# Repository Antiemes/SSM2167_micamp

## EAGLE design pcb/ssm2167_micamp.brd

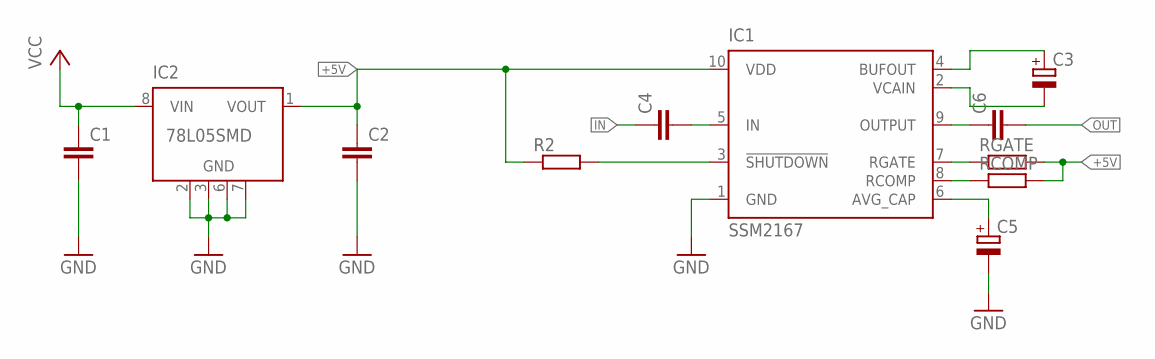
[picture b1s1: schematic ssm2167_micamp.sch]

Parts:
C1, C2: C-EUC0603K; C0603K
C3, C5: CPOL-EUE; PANASONIC_E
C4, C6: C-EUC1812; C1812
IC1: SSM2167; SO10
IC2: 78L05SMD; SO08
R2: R-EU_M1206; M1206
RCOMP: R-EU_M1206; M1206
RGATE: R-EU_M1206; M1206

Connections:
+5V: C2.1, IC1.10 (VDD), IC2.1 (VOUT), R2.1, RCOMP.2, RGATE.2
GND: C1.2, C2.2, C5.-, IC1.1 (GND), IC2.2 (GND), IC2.3 (GND), IC2.6 (GND), IC2.7 (GND)
IN: C4.1
unnamed: IC1.3 (!SHUTDOWN), R2.2
unnamed: IC1.7 (RGATE), RGATE.1
unnamed: IC1.8 (RCOMP), RCOMP.1
unnamed: C3.+, IC1.4 (BUFOUT)
unnamed: C3.-, IC1.2 (VCAIN)
unnamed: C4.2, IC1.5 (IN)
unnamed: C5.+, IC1.6 (AVG_CAP)
unnamed: C6.1, IC1.9 (OUTPUT)
OUT: C6.2
VCC: C1.1, IC2.8 (VIN)

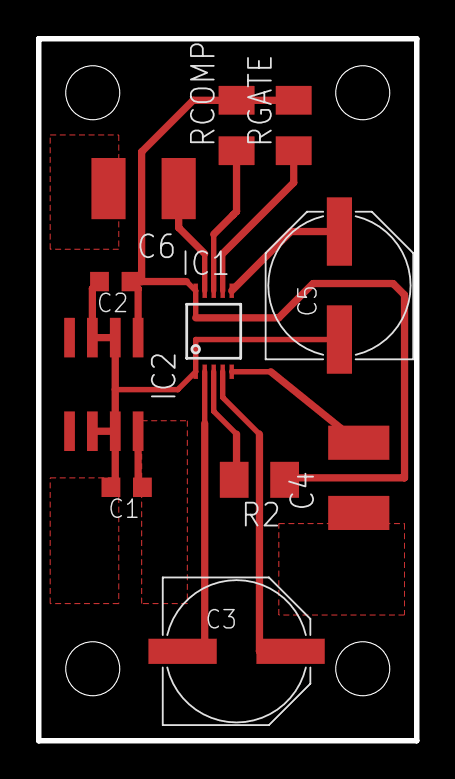
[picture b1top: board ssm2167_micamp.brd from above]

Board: 2 copper layers, 21.0 x 39.0 mm, 11 parts (0 on the bottom side), 11 nets.

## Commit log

2020-05-17 Initial commit.
